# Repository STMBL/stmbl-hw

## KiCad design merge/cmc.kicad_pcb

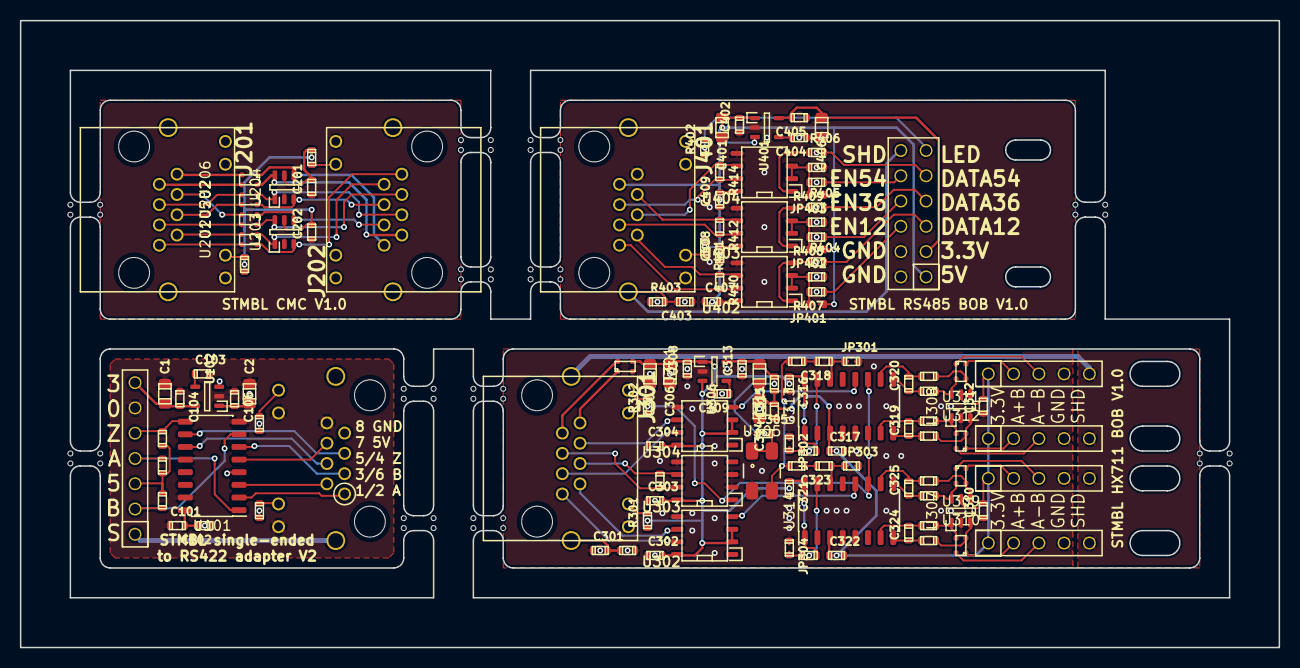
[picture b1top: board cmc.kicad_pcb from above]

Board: 4 copper layers, 126.5 x 63.0 mm, 174 parts (1 on the bottom side), 92 nets.

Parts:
C1, C2, C306, C307, C311, C314, C401, C406: 10u; C_0805
C101, C103, C104, C106, C201, C202, C301, C302, C303, C304, C305, C308, C310, C312, C313, C316, C317, C319, C320, C321, C322, C324, C325, C402, C403, C404, C405, C407, C408, C409: 100n; C_0603
C102: 1u; C_0603
C309: 100p; C_0603
C315: 2.2u; C_0603
C318, C323: 20pf; C_0603
J101: CONN_01X07; Pin_Header_RM2.54_1x7_UP
J102, J201, J202, J301, J401: RJ45_LED
J302, J303, J304, J305: CONN_01X05; Pin_Header_RM2.54_1x5_UP
J402: CONN_02X06_Odd_Even; Pin_Header_RM2.54_2x6_UP
JP301, JP302, JP303, JP304, JP401, JP402, JP403: Jumper_NO_Small; 0603_jumper
L301: INDUCTOR; R_0603
R101, R102, R103: 3.9k; R_0603
R104, R105, R201, R202: 560; R_0603
R301, R302, R401, R402: 560; C_0603
R303, R304, R307, R308, R309, R310, R313, R314, R315, R316: 120; R_0603
R305, R306, R311, R312, R411, R413, R415: 1k; R_0603
R403, R404, R405, R406, R407, R408, R409, R410, R412, R414: 120; C_0603
U24, U24#2, U24#3, U24#4, U24#5, U24#6, U24#7, U24#8, U24#9, U24#10, U24#11, U24#12, U24#13, U24#14, U24#15, U24#16, U24#17, U24#18, U24#19, U24#20, U24#21, U24#22, U24#23, U24#24, U24#25, U24#26, U24#27, U24#28, U24#29, U24#30, U24#31, U24#32, U24#33, U24#34, U24#35, U24#36, U24#37, U24#38, U24#39, U24#40, U24#41, U24#42, U24#43, U24#44, U24#45, U24#46, U24#47, U24#48: non_plated; non_plated_1mm
U101: am26ls31; SOIC-16
U102, U306, U401: LDO; SOT-23-5
U201, U202, U205, U206, U301, U309, U310, U311, U312: CMC; CMC_0805
U203, U204, U307, U308: USBLC6-4SC6; SOT-23-6
U302, U303, U304, U402, U403, U404: sp485; SOIC-8-N
U305: 20M; Oscillator_SMD_0603_4Pads
U313, U314: HX711; SOIC-16

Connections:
1: J201.1, J301.1, J401.1, R410.1, U201.3, U302.7, U402.7
1_1: J202.1, U201.4, U203.3
2: J201.2, J301.2, J401.2, R410.2, U201.2, U302.6, U402.6
2_2: J202.2, U201.1, U203.1
3: J201.3, J301.3, J401.3, R412.1, U205.3, U304.7, U403.7
3_3: J202.3, U203.6, U205.4
4: J201.4, J301.4, J401.4, R304.2, R414.2, U202.3, U303.6, U404.6
4_4: J202.4, U202.4, U204.3
5: J201.5, J301.5, J401.5, R304.1, R414.1, U202.2, U303.7, U404.7
5_5: J202.5, U202.1, U204.1
6: J201.6, J301.6, J401.6, R412.2, U205.2, U304.6, U403.6
6_6: J202.6, U203.4, U205.1
7: J201.7, U206.3
7_7: J202.7, U204.6, U206.4
8: J201.8, U206.2
8_8: J202.8, U204.4, U206.1
13: J201.13, J202.13
+3.3VA: C310.1, C312.1, C314.1, C315.1, C317.2, C322.2, J302.1, J303.1, J304.1, J305.1, L301.2, U307.5, U308.5, U313.3, U314.3
+3V3: C1.1, C104.1, C201.1, C202.1, C305.1, C311.1, C313.1, C405.1, C406.1, J101.7, J402.3, L301.1, R201.2, R202.2, U102.5, U203.5, U204.5, U305.1, U305.4, U306.5, U401.5
+5V: C2.1, C101.1, C102.1, C106.1, C302.1, C303.1, C304.1, C306.1, C307.1, C308.1, C316.2, C321.2, C401.1, C402.1, C407.1, C408.1, C409.1, J101.3, J102.7, J401.7, J402.1, JP401.2, JP402.2, JP403.2, R101.1, R102.1, R103.1, R104.1, R301.2, R306.2, R312.2, R401.2, U101.4, U101.16, U102.1, U102.3, U301.3, U302.2, U302.3, U302.8, U303.8, U304.2, U304.3, U304.8, U306.1, U306.3, U313.1, U313.16, U314.1, U314.16, U401.1, U401.3, U402.8, U403.8, U404.8
A: J101.4, R101.2, U101.1
A1+: R313.2, U307.3, U309.2
A1-: R314.2, U307.1, U309.3
A2+: R307.2, U308.3, U311.2
A2-: R308.2, U308.1, U311.3
B: J101.2, R102.2, U101.7
B1+: R315.2, U307.4, U310.3
B1-: R316.2, U307.6, U310.2
B2+: R309.2, U308.4, U312.3
B2-: R310.2, U308.6, U312.2
DATA_12: R404.2, U402.1, U402.4
DATA_36: R405.2, U403.1, U403.4
DATA_54: R406.2, U404.1, U404.4
DOUT1: U302.4, U314.12
DOUT2: U304.4, U313.12
EN_12: JP401.1, R407.1, R411.2, U402.2, U402.3
EN_36: JP402.1, R408.1, R413.2, U403.2, U403.3
EN_54: JP403.1, R409.1, R415.2, U404.2, U404.3
GND: C1.2, C2.2, C101.2, C102.2, C103.1, C104.2, C106.2, C201.2, C202.2, C301.2, C302.2, C303.2, C304.2, C305.2, C306.2, C307.2, C308.2, C309.1, C310.2, C311.2, C312.2, C313.2, C314.2, C315.2, C316.1, C317.1, C321.1, C322.1, C401.2, C402.2, C403.2, C404.2, C405.2, C406.2, C407.2, C408.2, C409.2, J101.6, J102.8, J102.9, J102.11, J201.11, J202.11, J301.9, J301.11, J302.4, J303.4, J304.4, J305.4, J401.8, J401.9, J401.11, J402.2, J402.4, JP301.1, JP302.2, JP303.1, JP304.2, R303.2, R403.2, R411.1, R413.1, R415.1, U101.8, U101.12, U101.15, U102.2, U203.2, U204.2, U301.2, U302.5, U303.2, U303.3, U303.5, U304.5, U305.2, U306.2, U307.2, U308.2, U313.4, U313.5, U314.4, U314.5, U401.2, U402.5, U403.5, U404.5
GNDA: J101.1, J102.13
GNDS: C301.1, C403.1, J301.13, J302.5, J303.5, J304.5, J305.5, J401.13, J402.12, R303.1, R403.1
IDX: J101.5, R103.2, U101.9
LED: J402.11, R402.2
unnamed: C103.2, U102.4
unnamed: C309.2, U306.4
unnamed: C318.1, R305.2
unnamed: C318.2, JP301.2, U313.14
unnamed: C319.1, R308.1, U313.7
unnamed: C319.2, R307.1, U313.8
unnamed: C320.1, R309.1, U313.10
unnamed: C320.2, R310.1, U313.9
unnamed: C323.1, R311.2
unnamed: C323.2, JP303.2, U314.14
unnamed: C324.1, R314.1, U314.7
unnamed: C324.2, R313.1, U314.8
unnamed: C325.1, R315.1, U314.10
unnamed: C325.2, R316.1, U314.9
unnamed: C404.1, U401.4
unnamed: J102.1, U101.2
unnamed: J102.2, U101.3
unnamed: J102.3, U101.6
unnamed: J102.4, U101.11
unnamed: J102.5, R105.1, U101.10
unnamed: J102.6, U101.5
unnamed: J102.10, R105.2
unnamed: J102.12, R104.2
unnamed: J201.12, R201.1
unnamed: J202.12, R202.1
unnamed: J301.7, U301.4
unnamed: J301.8, U301.1
unnamed: J301.10, R302.1
unnamed: J301.12, R301.1
unnamed: J302.2, U309.1
unnamed: J302.3, U309.4
unnamed: J303.2, U310.4
unnamed: J303.3, U310.1
unnamed: J304.2, U311.1
unnamed: J304.3, U311.4
unnamed: J305.2, U312.4
unnamed: J305.3, U312.1
unnamed: J401.10, R402.1
unnamed: J401.12, R401.1
unnamed: J402.5, R404.1
unnamed: J402.6, R407.2
unnamed: J402.7, R405.1
unnamed: J402.8, R408.2
unnamed: J402.9, R406.1
unnamed: J402.10, R409.2
unnamed: JP302.1, R306.1, U313.15
unnamed: JP304.1, R312.1, U314.15
SCK: R302.2, U303.1, U313.11, U314.11
XSCK: R305.1, R311.1, U305.3

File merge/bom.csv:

Comment,Designator,Footprint,LCSC
"RJ45_LED RJ45_LED","J201 J202 J102 J301 J401","RJ45_LED",
"USBLC6-4SC6 SOT-23-6","U203 U204 U307 U308","SOT-23-6",C111212
"100n C_0603","C201 C202 C106 C101 C104 C103 C302 C313 C308 C305 C310 C312 C303 C304 C301 C319 C320 C317 C316 C324 C325 C322 C321 C403 C404 C405 C402 C407 C408 C409","C_0603",C14663
"CMC CMC_0805","U201 U205 U202 U206 U309 U310 U311 U312 U301","CMC_0805",C80529
"560 R_0603","R201 R202 R104 R105","R_0603",C23204
"CONN_01X07 Pin_Header_RM2.54_1x7_UP","J101","Pin_Header_RM2.54_1x7_UP",
"3.9k R_0603","R101 R102 R103","R_0603",C23018
"am26ls31 SOIC-16","U101","SOIC-16",C6179
"1u C_0603","C102","C_0603",C15849
"LDO SOT-23-5","U102 U306 U401","SOT-23-5",C9055
"10u C_0805","C2 C1 C311 C307 C314 C306 C401 C406","C_0805",C15850
"sp485 SOIC-8-N","U302 U303 U304 U402 U403 U404","SOIC-8-N",C6855
"20M Oscillator_SMD_0603_4Pads","U305","Oscillator_SMD_0603_4Pads",C32529
"INDUCTOR R_0603","L301","R_0603",C73100
"120 R_0603","R303 R304 R307 R308 R309 R310 R313 R314 R315 R316","R_0603",C22787
"2.2u C_0603","C315","C_0603",C23630
"560 C_0603","R302 R301 R402 R401","C_0603",C23204
"CONN_01X05 Pin_Header_RM2.54_1x5_UP","J302 J303 J304 J305","Pin_Header_RM2.54_1x5_UP",
"100p C_0603","C309","C_0603",C14858
"HX711 SOIC-16","U313 U314","SOIC-16",C43656
"1k R_0603","R306 R305 R312 R311 R411 R413 R415","R_0603",C21190
"Jumper_NO_Small 0603_jumper","JP302 JP301 JP304 JP303 JP401 JP402 JP403","0603_jumper",
"20pf C_0603","C318 C323","C_0603",C1648
"120 C_0603","R403 R404 R405 R406 R407 R408 R409 R410 R412 R414","C_0603",C22787
"CONN_02X06_Odd_Even Pin_Header_RM2.54_2x6_UP","J402","Pin_Header_RM2.54_2x6_UP",
